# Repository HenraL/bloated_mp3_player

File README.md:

<!-- 
-- +==== BEGIN Bloated MP3 Player =================+
-- LOGO:
-- .......................
-- ...><>.............<><.
-- ..><>.><>.......<><.<><
-- .><>.<><.><>.<><.<><.<>
-- ..><>.><>.......<><.<><
-- ...><>.............<><.
-- .......................
-- /STOP
-- PROJECT: Bloated MP3 Player
-- FILE: README.md
-- CREATION DATE: 23-07-2026
-- LAST Modified: 14:19:29 01-09-2026
-- DESCRIPTION:
-- This is the code in charge of making the bloated player come to life.
-- /STOP
-- COPYRIGHT: (c) Henry Letellier
-- PURPOSE: This is the file that presents and explains the projects aim.
-- // AR
-- +==== END Bloated MP3 Player =================+
-->
# **DON'T PANIC**

## bloated_mp3_player

> **The answer is 42. The question, it turns out, is: "How many peripherals can you bolt onto an ESP32 before the scheduler files for divorce?"**

This is a multithreaded embedded project that started life as a humble MP3 player and, through a series of unfortunate events vaguely resembling a real-time systems course, accreted so many non-essential components that it now requires a concurrent scheduler just to keep them all arguing fairly for CPU time.

It runs on an ESP32-S3 (the electronic equivalent of an Infinite Improbability Drive, only slightly less likely to turn you into a potted plant or a philosophical whale), uses FreeRTOS under the hood (courtesy of the Arduino framework), and demonstrates that you can, in fact, teach concurrency by strapping seventeen unrelated sensors to a single I²C bus and hoping for the best.

## Contents

> *"Please read the signs before panic."*

- [About](#about) — why a Vogon would raise an eyebrow
- [Disclaimer](#disclaimer) — we tried to warn you
- [Dependencies](#dependencies) — the unhealthy soil it all grows in
- [Components Used](#components-used) — the BOM of doomed hardware
- [Divorce proceedings](#divorce-proceedings) — a strained peripheral marriage
- [How to Flash](#how-to-flash) — the very real thermonuclear toolchain
- [How to Use](#how-to-use) — but there is no off switch
- [Bonus Tools](#bonus-tools) — flamegraphs & baked fonts
- [License](#license) — so long, and thanks for all the fish

## About

> *"The ships hung in the sky in much the same way that bricks don't."*
> — Douglas Adams, *The Hitchhiker's Guide to the Galaxy*

This program is a multithreaded C++ monstrosity for the Real Time Embedded Systems course at **Unimore Enzo Ferrari AI and engineering department**. It was inspired by *The Hitchhiker's Guide to the Galaxy* not because it does anything particularly galactic, but because the sheer quantity of peripherals tacked onto it would make even a Vogon constructor fleet raise an eyebrow.

The core mission: play MP3s from a microSD card while simultaneously monitoring temperature, humidity, air pressure, rotation, acceleration, magnetic fields, and the existential dread of a WS2812B RGB matrix trying to decide what colour to be or where to put the bablefish.

Is it practical? No.
Does it demonstrate concurrency? Absolutely.
Would Zaphod Beeblebrox approve? Almost certainly, right before stealing it.

## Disclaimer

- This program is provided **as is**, without warranty of any kind — implied, express, or Vogon-constructed. If your ESP32 achieves sentience and demands a better quality MP3 files, that's your problem.
- This program was written with the assistance of AI. The AI is not responsible for any design decisions, but it did try to talk us out of the 16×16 RGB matrix. We didn't listen.
- Developed under **Ubuntu 24.04.4 LTS**, where ESP32s tend to materialise on `/dev/ttyACM0` (unless they're feeling contrary, in which case check `dmesg`).
- Targeted at the **ESP32-S3 WROOM FREENOVE** dev board. Flashed via the PlatformIO extension for VS Code (or however one normally communicates with small, irritable computers).
- The [KiCad schematic](./hardware/) is provided as a wiring reference. You could send it to a PCB manufacturer if you're feeling brave, but the author (and his AI accomplice) accept no responsibility for design issues, misplaced vias, or spontaneous combustion.
- Components are universally sourcable from websites such as Amazon, AliExpress, or (for the truly adventurous) by flagging down a passing Dentrassi supply ship.

## Dependencies

The software stack, from bottom to top:

| Layer | What it is | Why it's here |
| ------- | ----------- | --------------- |
| FreeRTOS | Real-time OS (via Arduino) | So 17 tasks can deadlock each other in style |
| Arduino ESP32 Core | HAL / framework | Because writing raw ESP-IDF is for people with more patience |
| [Adafruit NeoPixel](https://github.com/adafruit/Adafruit_NeoPixel) | RGB LED control | Makes the matrix glow reassuringly |
| [U8g2](https://github.com/olikraus/u8g2) | OLED/LCD monochrome graphics | Draws text and badly-scaled album art on the 128×64 LCD |
| [arduino-libhelix](https://github.com/pschatzmann/arduino-libhelix) | Fixed-point MP3 decoder | Helix-based MP3 decoding with PSRAM support; because software decoding without it is like a Vogon without a thesaurus |

Most library dependencies materialise automagically from the PlatformIO ether. The exception is the one that does the actual heavy lifting — see the submodule note below, and try not to think about what happens if you forget `--recursive`.

### Git Submodule: arduino-libhelix

> *"The major difference between a thing that might go wrong and a thing that cannot possibly go wrong is that when a thing that cannot possibly go wrong goes wrong, it usually turns out to be impossible to get at or repair."*
> — Douglas Adams, *Mostly Harmless*

This library lives at `platformio/bloated_mp3_player/lib/arduino-libhelix` and is not a PlatformIO registry package — it is, officially, A Thing That Cannot Possibly Go Wrong.

To initialise it (and thereby disprove the above quote):

```bash
git clone --recursive <repository-url>
```

If you cloned without `--recursive` (you magnificent fool):

```bash
git submodule update --init --recursive
```

PlatformIO scans `lib/` automatically, so the submodule compiles itself into the firmware with no further configuration. If this sounds too easy, re-read the quote at the top of this section.

## Components Used

> *"The Guide is definitive. Reality is frequently inaccurate."*
> — *The Hitchhiker's Guide to the Galaxy*

The following have been sacrificed on the altar of concurrency:

| Purpose | Name | Price (€) | Quantity | Link |
| --------- | ------ | ----------- | ---------- | ------ |
| :brain: The brains | Freenove ESP32-S3-WROOM CAM — Dual-core 32-bit 240 MHz | 20.19 | 1 | [AliExpress](https://aliexpress.com/item/1005004960637276.html) |
| :tv: Display | Lcd12864 12864-06D — COG dot matrix, SPI, with Chinese font | 6.19 | 1 | [AliExpress](https://aliexpress.com/item/1005009024477658.html) |
| :receipt: Cash-register display | TZT LCD2004+I2C — 2004A 20x4 HD44780 char LCD with I2C adapter soldered on the back | 4.85 | 1 | [AliExpress](https://aliexpress.com/item/1005004726086089.html) |
| :scroll: Vogon ticker | LCD1602+I2C Module — 16x2 HD44780 char LCD, PCF8574T IIC interface, 5 V (blue, I2C soldered on the back) | 2.63 | 1 | [AliExpress](https://aliexpress.com/item/1005006170395488.html) |
| :thermometer: Weather station | AHT20+BMP280 — Temperature, humidity & air pressure | 1.20 | 1 | [AliExpress](https://aliexpress.com/item/1005007702473893.html) |
| :triangular_ruler: Distance | HC-SR04 — Ultrasonic "how far is the wall" sensor | 1.41 | 1 | [AliExpress](https://aliexpress.com/item/1005007849944952.html) |
| :arrows_counterclockwise: User input | EC11 Rotary Encoder with switch — 20 positions, knob shaft | 3.49 | 1 | [AliExpress](https://aliexpress.com/item/1005004908084537.html) |
| :loud_sound: Crappy beeps | 4Ω 3W / 8Ω 2W cavity speaker — tiny, tinny, test-tones only | 1.38 | 2 | [AliExpress](https://aliexpress.com/item/1005008626624201.html) |
| :compass: Orientation | GY-9250 MPU-9250 — 9-axis gyro + accel + magnetometer | 3.09 | 1 | [AliExpress](https://aliexpress.com/item/1005007211455522.html) |
| :flashlight: Light show | WS2812B 16×16 RGB LED matrix — individually addressable chaos | 14.39 | 1 | [AliExpress](https://aliexpress.com/item/1005005394534715.html) |
| :floppy_disk: Storage | Micro SD Card Module — SPI level-shifted | 1.24 | 1 | [AliExpress](https://aliexpress.com/item/1005010653353565.html) |

**Total carnage:** ~€62.06 plus fuses, caps, and whatever else you inevitably forgot.

The two character displays (2004A + 1602A) arrive with their I2C adapter boards pre-soldered on the back, so no extra PCF8574 wiring is needed — just VCC/GND/SDA/SCL to the bus. Mind the addresses though: they ship defaulted to 0x27, so the second one needs the A0 pad bridged (0x26) to live on the same bus as the first.

For fuses, capacitors, resistors, and the 5 V → 3.3 V regulators, see the schematic. You probably have them in a drawer somewhere. The author assumes no responsibility for the state of that drawer.

### Divorce proceedings

> *"I am the President of the Galaxy. I'm not in the mood for a diplomatic relationship."*

Despite our best efforts, the development prototype has filed for divorce with two of its peripherals: the STN 128×64 LCD and the WS2812B matrix have gone silent (presumably due to wiring disagreements). The firmware driving both of them is still running, faithfully poking the pins every task tick — so if the wiring ever is reconciled, they may snap back to life like nothing happened. No firmware update required. Just cable therapy.

The I2C character displays, meanwhile, have fully reconciled: the 2004A info panel (folder browser, track names, volume, uptime) and the 1602A Vogon poetry panel (which also breathes IMU orientation readouts between stanzas) are both happily married to the bus. If the big LCD and matrix ever announce a reconciliation, this entry will be updated accordingly.

## How to Flash

> *"A towel is about the most massively useful thing an interstellar hitchhiker can have."*

1. Load some `.mp3` files onto a microSD card. 44.1 kHz, 16-bit stereo is the recommended flavour of the universe.
2. Insert the card into the ESP32's SD card reader (or the module you soldered on after muttering imprecations at the pinout).
3. Open the project in VS Code with the PlatformIO extension installed. If you don't have PlatformIO, you're about to have a Very Bad Time.
4. Connect your ESP32. There are usually two USB ports: one for UART (debug) and one for OTG (flash). **The OTG one is the one you want.** If you get it wrong, nothing explodes — you'll just get a timeout. This is fine.
5. Locate the **`→`** arrow at the bottom of the VS Code window. Click it. This compiles the firmware and, if the stars align, flashes it to the board.
6. If the flash fails: check the port, hold the BOOT button, and try again. Repeat until the universe stops playing tricks on you.

### Pre-flight flash erase

A PlatformIO extra script (`middleware/full_erase.py`) automatically erases the ESP32's flash before each upload. This ensures no stale data haunts your new firmware like the ghost of a Vogon poem.

It can also be run standalone:

```bash
python middleware/full_erase.py                          # auto-detect port
python middleware/full_erase.py --port /dev/ttyUSB0      # explicit port
```

It will find `esptool.py` in your PATH, or tell you to `pip install esptool` if you haven't.

## How to Use

> *"In the beginning, the universe was created. This has made a lot of people very angry and been widely regarded as a bad move."*

Turn the rotary encoder to navigate. Selection is two-stage: rotate to pick a
folder (album), press once to step inside and browse its tracks, rotate to the
track you want, press again to play it. Double- or triple-click the knob to skip
forward/back a track while playing (or to pop back to the album list while
browsing inside a folder). Wave a hand once past the ultrasonic sensor to pause,
and wave it twice quickly to abandon the current track and return to the menu.

The interface appears on the SPI LCD and the 2004A info panel, which shows the
current folder, track, volume and uptime (hh:mm:ss). The 1602A recites Vogon
poetry and periodically trades buffers with the IMU to show roll/pitch/yaw. The
RGB matrix will do something presumably artistic if its wiring ever gets talked
off the ledge. The ultrasonic sensor will judge your distance from the board.
The MPU-9250 will ponder its orientation in the cosmos. The temperature sensor
will inform you that it is, in fact, room temperature.

There is no off switch. You have been warned.

## Bonus Tools

### Flamegraph Profiling (bonus/extras/flamegraph.py)

The firmware includes a lightweight profiler that can dump task timing traces and CPU usage stats over the serial port. The `flamegraph.py` script converts that output into an interactive SVG flamegraph — a visual representation of where the CPU is spending its time (or, as the Guide would put it, "how the microprocessor is frittering away the microseconds").

**To capture profiling data:**

1. In the firmware, ensure `Profiling::dump_traces()` or `Profiling::dump_task_stats()` is called. The output appears on the serial console (typically 115200 baud) in sections bracketed by `=== PROFILING TRACES ===` / `=== END PROFILING TRACES ===`.
2. Save that serial output to a file:

   ```bash
   platformio device monitor --raw > serial_dump.txt
   ```

   Press the reset button to trigger the dump, then hit Ctrl+C to stop.
3. Generate the flamegraph:

   ```bash
   python bonus/extras/flamegraph.py serial_dump.txt
   ```

   This produces `flamegraph.svg` (or `flamegraph_traces.svg` / `flamegraph_task_stats.svg` if multiple sections are present).
4. Open the SVG in any browser. The wider a bar, the more time that function consumed. Hover for details.

**Usage summary:**

```bash
python bonus/extras/flamegraph.py < serial_dump.txt              # read from stdin
python bonus/extras/flamegraph.py serial_dump.txt                # read from file
python bonus/extras/flamegraph.py serial_dump.txt -o output.svg  # custom output
```

### Image & Font Conversion (bonus/ dir)

> *"The ships hung in the compiler's symbol table in much the same way that bricks don't."*
> — The Maker's Guide to the Codebase

Two Python converters that perform the digital equivalent of the Total Perspective Vortex:
they take your PNGs and TTF/OTF fonts, shrink them down to their essential C byte-array
essence, and embed them directly into the firmware. No filesystem reads. No SD card
dependency. Just pure, uncompromising, flash-resident data.

Use the provided shell scripts — they create their own virtual environment from
`requirements.txt`, install Pillow and fonttools, run the converter, then clean up
after themselves. Like a well-mannered Vogon butler.

| If you want to | Run this | It auto-creates venv from |
| --- | --- | --- |
| Bake fonts into C | `./bonus/font2c.sh` | `bonus/font2c/requirements.txt` |
| Bake images into C | `./bonus/img2c.sh` | `bonus/img2c/requirements.txt` |

---

#### Font → C (`bonus/font2c.sh` / `bonus/font2c/convert.py`)

Converts TTF/OTF fonts into a PlatformIO C library. Each glyph becomes a compact
bitmap; widths are proportional, the living is easy, and the flash usage is only
moderately horrifying.

**Quickest path to enlightenment:**

```bash
./bonus/font2c.sh
```

This processes every font in `bonus/fonts/` at point sizes 2 through 20 (step 2)
and deposits the resulting C library into `lib/fonts/`. The noise you hear is
Pillow rendering approximately 500 glyphs per size per font. Have a towel ready.

**Single font, specific size:**

```bash
./bonus/font2c.sh bonus/fonts/Tiny5/Tiny5-Regular.ttf lib/fonts/ --size 14
```

**What you can tweak:**

| Flag | Default | What it does (in plain Galactic) |
| ------ | --------- | ---------------------------------- |
| `--size SIZE` | — | Exactly one point size; ignores `--min`/`--max` |
| `--min MIN` | 8 | Smallest size to generate |
| `--max MAX` | 20 | Largest size to generate |
| `--step STEP` | 2 | Step between sizes (2 = 8, 10, 12, …) |
| `--first FIRST` | 32 (space) | First Unicode code point to include |
| `--last LAST` | 0x10FFFF | Last Unicode code point (yes, that's the whole of Unicode) |
| `--batch` | — | Recursively find all TTF/OTF in the input directory |
| `--no-extern` | — | Stuff everything into the headers (no separate .cpp) |
| `--no-progmem` | — | Omit PROGMEM (if you hate flash and love RAM) |

**What lands in `lib/fonts/`:**

```plaintext
lib/fonts/
├── include/
│   ├── fonts.hpp              — Master include (include this, get all)
│   ├── font_structs.hpp       — FontHandle, RenderedGlyph, and friends
│   ├── font_constants.hpp     — Size and style constants
│   ├── font_families.hpp      — Family cross-reference tables
│   ├── font_helpers.hpp       — find_font(), get_glyph() & co.
│   └── internal/<family>/
│       └── <family>_<size>pt.hpp  — Per-size declarations
├── src/
│   └── <family>_<size>pt.cpp  — Actual bit data + FontHandle
├── library.json
└── CMakeLists.txt
```

**Manual run (if you distrust shell scripts — and who can blame you?):**

```bash
python3 -m venv .venv
. .venv/bin/activate
pip install -r bonus/font2c/requirements.txt
python bonus/font2c/convert.py bonus/fonts/Tiny5/Tiny5-Regular.ttf lib/fonts/ --size 14
deactivate
```

---

#### Image → C (`bonus/img2c.sh` / `bonus/img2c/convert.py`)

Turns PNGs into C byte arrays. Each image gets two representations:

- **1-bit packed bitmap** — 8 pixels per byte, perfect for the 128×64 LCD
- **8-bit grayscale** — for when you eventually want to dither like a Vogon
  constructor fleet painting a bypass

**Quick start:**

```bash
./bonus/img2c.sh
```

Every PNG in `bonus/images/` gets converted and packed into `lib/images/` as a
PlatformIO library. If the images had towels, they'd be packed too.

**Single file:**

```bash
./bonus/img2c.sh bonus/images/baseline_menu_black_48dp.png --output lib/images/
```

**Available levers:**

| Flag | Default | Description |
| ------ | --------- | ------------- |
| `-o DIR`, `--output DIR` | — | Where to put the result |
| `--batch` | — | Process all PNGs in input directory |
| `--library` | — | Generate `include/` + `src/` PlatformIO structure |
| `--no-gray` | — | Skip the grayscale array |
| `--no-bits` | — | Skip the 1-bit packed array |
| `--gen-source FILE` | — | One `.cpp` to rule them all |
| `--no-extern` | — | Inline everything in headers |
| `--no-progmem` | — | No PROGMEM (RAM is a dish best served cold) |

**Output terrain:**

```plaintext
lib/images/
├── include/
│   ├── images.hpp                 — Aggregated master header
│   └── internal/
│       └── baseline_menu_black_48dp.hpp  — Per-image header
├── src/
│   └── images.cpp                 — Bit data definitions
├── library.json
└── CMakeLists.txt
```

**Manual run (for the autonomously inclined):**

```bash
python3 -m venv .venv
. .venv/bin/activate
pip install -r bonus/img2c/requirements.txt
python bonus/img2c/convert.py bonus/images/ lib/images/ --batch --library
deactivate
```

> **A note on virtual environments:**
> Your operating system's Python is a precious and temperamental ecosystem —
> rather like a Babel fish, but less useful at translating Vogon poetry.
> Do not install random packages into it. Use the shell scripts (they handle
> everything) or create a temporary venv manually. The universe will thank you.
> Probably.

## License

> *"So long, and thanks for all the fish."*

This project is licensed under the [MIT License](./LICENSE). Do what you like with it. If you build something cool, tell the dolphins.

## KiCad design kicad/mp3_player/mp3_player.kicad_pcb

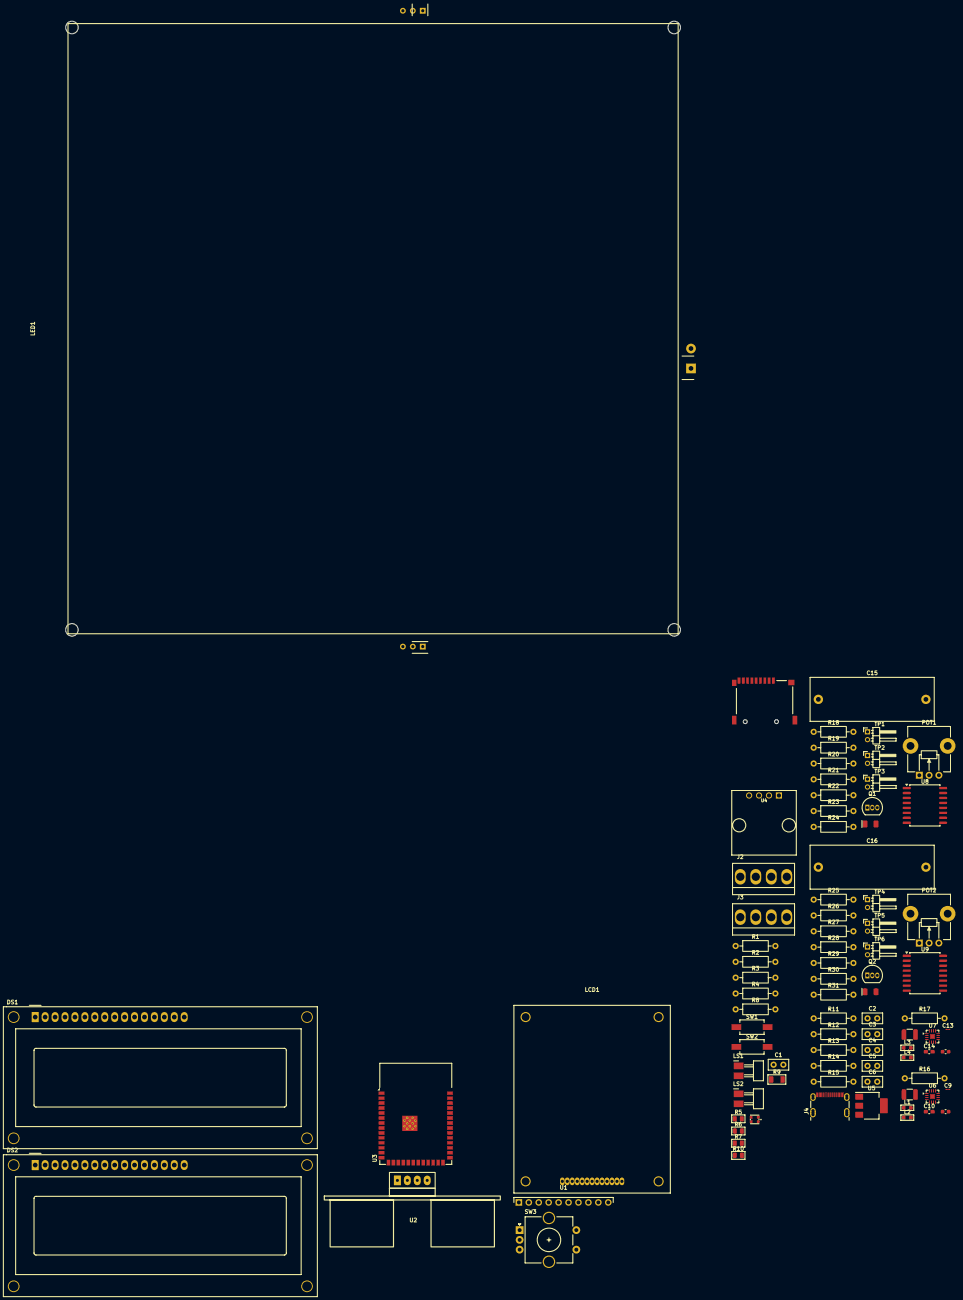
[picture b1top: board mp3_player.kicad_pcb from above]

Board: 2 copper layers, 86 parts (0 on the bottom side), 80 nets, no tracks yet.

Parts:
C1: 100nF_Ceramic; C_Disc_D5.0mm_W2.5mm_P2.50mm
C2: 1nF_Ceramic; C_Disc_D5.0mm_W2.5mm_P2.50mm
C3, C5: 10uF; C_Disc_D5.0mm_W2.5mm_P2.50mm
C4, C6: 100nF; C_Disc_D5.0mm_W2.5mm_P2.50mm
C7, C11: 10uF; C_1210_3225Metric
C8, C12: 0.1uF; C_0603_1608Metric
C9, C13: 220pF_0603_25V; C_01005_0402Metric_Pad0.57x0.30mm_HandSolder
C10, C14: 220pF_0603_25V; C_0603_1608Metric_Pad1.08x0.95mm_HandSolder
C15, C16: 0.1uF; C_Rect_L31.5mm_W11.0mm_P27.50mm_MKS4
D1: WS2812B; WS2812_2020
D2, D3: Blue; LED_1206_3216Metric_Blue
DS1: WC2004A; WC1602A
DS2: WC1602A
J1: microSD; microSD_External_Pin
J2, J3: Conn_01x04; Pins_1x04_3.96mm_TH_MTA156
J4: Conn_USB_C_Socket; Conn_USB_C_Socket_Molex_2171790001
L1, L2, L3, L4: 33nH; R_0603_1608Metric_Pad0.98x0.95mm_HandSolder
LCD1: LCD-13pin; LCD_1x13_P1.27mm_Vertical
LED1: LED_Matrix_16x16_WS2812B
LS1, LS2: Speaker; PinHeader_01x02_P2.54mm_Horizontal_SMD
POT1, POT2: 16mm_CtrDet_10k; Potentiometer_TT_P0915N
Q1, Q2: S8050; TO-92_Inline
R1: 2.2k; R_Axial_DIN0207_L6.3mm_D2.5mm_P10.16mm_Horizontal
R2, R18, R19, R20, R22, R25, R26, R27, R29: 1k; R_Axial_DIN0207_L6.3mm_D2.5mm_P10.16mm_Horizontal
R3, R4: 4.7k; R_Axial_DIN0207_L6.3mm_D2.5mm_P10.16mm_Horizontal
R5, R6, R7, R10: R_0805; R_0805_2012Metric
R8: 220ohm; R_Axial_DIN0207_L6.3mm_D2.5mm_P10.16mm_Horizontal
R9: R_1206; R_1206_3216Metric
R11, R16, R17: 1M; R_Axial_DIN0207_L6.3mm_D2.5mm_P10.16mm_Horizontal
R12, R13: 5.1k; R_Axial_DIN0207_L6.3mm_D2.5mm_P10.16mm_Horizontal
R14, R15: 10k; R_Axial_DIN0207_L6.3mm_D2.5mm_P10.16mm_Horizontal
R21, R23, R24, R28, R30, R31: 47k; R_Axial_DIN0207_L6.3mm_D2.5mm_P10.16mm_Horizontal
SW1: Boot; Button_CnK_PTS636.0_6x3.5mm
SW2: Reset; Button_CnK_PTS636.0_6x3.5mm
SW3: RotaryEncoder_Switch; RotaryEncoder_Alps_EC11E-Switch_Vertical_H20mm_CircularMoun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
TP1, TP2, TP3, TP4, TP5, TP6: TestPoint_2Pole; PinHeader_1x02_P2.00mm_Horizontal
U1: MPU6500-breakout; GY-6500_1x10_P2.54mm_Vertical
U2: HC-SR04_Ultrasonic_Sensor
U3: ESP32-S3-WROOM-1
U4: AHT20_BMP280
U5: AMS1117-3.3; SOT-223-3_TabPin2
U6, U7: MAX98357A; TQFN-16-1EP_3x3mm_P0.5mm_EP1.23x1.23mm
U8, U9: PCF8574T; SOIC-16W_7.5x10.3mm_P1.27mm

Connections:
5V: C3.1, C7.2, C8.2, C11.2, C12.2, C15.1, C16.1, D2.2 (A), D3.2 (A), DS1.2 (VDD), DS1.15 (LED(+)), DS2.2 (VDD), J2.2, J3.2, J4.A4 (VBUS), J4.A9 (VBUS), J4.B4 (VBUS), J4.B9 (VBUS), LED1.1 (5V_IN), POT1.1 (Left), POT2.1 (Left), R16.1, R16.2, R17.1, R17.2, R19.1, R20.1, R21.2, R22.1, R23.2, R24.1, R26.1, R27.1, R28.2, R29.1, R30.2, R31.1, U2.1 (VCC), U6.4 (~SD_MODE), U6.7 (VDD), U6.8 (VDD), U7.4 (~SD_MODE), U7.7 (VDD), U7.8 (VDD), U8.16 (VDD), U9.16 (VDD)
/ESP power/EN: R14.2, SW2.2
/ESP power/ESP32_USB_D+: J4.A6 (Dp1), J4.B7 (Dn2), U3.14 (USB_D+)
/ESP power/ESP32_USB_D-: J4.A7 (Dn1), J4.B6 (Dp2), U3.13 (USB_D-)
/ESP power/IO0: R15.2, SW1.2
/I2C1/(K) BL-: DS1.16 (LED(-)), Q2.3 (C)
/I2C1/A0: R26.2, TP4.1, U9.1 (A0)
/I2C1/A1: R27.2, TP5.1, U9.2 (A1)
/I2C1/A2: R29.2, TP6.1, U9.3 (A2)
/I2C1/DB4: DS1.11 (D4), U9.9 (P4)
/I2C1/DB5: DS1.12 (D5), U9.10 (P5)
/I2C1/DB6: DS1.13 (D6), U9.11 (P6)
/I2C1/DB7: DS1.14 (D7), U9.12 (P7)
/I2C1/E: DS1.6 (E), U9.6 (P2)
/I2C1/RS: DS1.4 (RS), U9.4 (P0)
/I2C1/R/W: DS1.5 (R/W), U9.5 (P1)
/I2C1/V0: DS1.3 (VO), POT2.2 (Center)
/I2C/(K) BL-: DS2.16 (LED(-)), Q1.3 (C)
/I2C/A0: R19.2, TP1.1, U8.1 (A0)
/I2C/A1: R20.2, TP2.1, U8.2 (A1)
/I2C/A2: R22.2, TP3.1, U8.3 (A2)
/I2C/DB4: DS2.11 (D4), U8.9 (P4)
/I2C/DB5: DS2.12 (D5), U8.10 (P5)
/I2C/DB6: DS2.13 (D6), U8.11 (P6)
/I2C/DB7: DS2.14 (D7), U8.12 (P7)
/I2C/E: DS2.6 (E), U8.6 (P2)
/I2C/RS: DS2.4 (RS), U8.4 (P0)
/I2C/R/W: DS2.5 (R/W), U8.5 (P1)
/I2C/SCL: J2.4, J3.4, R3.1, R23.1, R30.1, U1.3 (SCL), U1.6 (ECL), U3.39 (IO1), U4.SCL, U8.14 (SCL), U9.14 (SCL)
/I2C/SDA: J2.3, J3.3, R4.1, R21.1, R28.1, U1.4 (SDA), U1.5 (EDA), U3.38 (IO2), U4.SDA, U8.15 (SDA), U9.15 (SDA)
/I2C/V0: DS2.3 (VO), POT1.2 (Center)
/MAX98357/BCLK: U3.9 (IO16), U6.16 (BCLK), U7.16 (BCLK)
/MAX98357/DIN: U3.11 (IO18), U7.1 (DIN)
/MAX98357/LRCLK: U3.24 (IO47), U6.14 (LRCLK), U7.14 (LRCLK)
/MAX98357/VD+: C13.1, L3.2, LS2.1
/MAX98357/VD-: C14.1, L4.2, LS2.2
/MAX98358/DIN: U3.10 (IO17), U6.1 (DIN)
/MAX98358/VD+: C9.1, L1.2, LS1.1
/MAX98358/VD-: C10.1, L2.2, LS1.2
GND: C2.1, C4.1, C7.1, C8.1, C9.2, C10.2, C11.1, C12.1, C13.2, C14.2, C15.2, C16.2, D1.2 (VSS), DS1.1 (VSS), DS2.1 (VSS), J1.6 (VSS), J1.10 (SHIELD), J2.1, J3.1, J4.A1 (GND), J4.A12 (GND), J4.B1 (GND), J4.B12 (GND), LCD1.7 (VSS), LCD1.9 (K), LED1.3 (GND_IN), LED1.6 (GND_OUT), LED1.8 (GND), POT1.3 (Right), POT2.3 (Right), Q1.1 (E), Q2.1 (E), R1.1, R11.1, R12.2, R13.2, R18.1, R25.1, SW3.C, SW3.S1, TP1.2, TP2.2, TP3.2, TP4.2, TP5.2, TP6.2, U1.2 (GND), U1.7 (AD0), U1.10 (FSYNC), U2.4 (GND), U3.1 (GND), U3.40 (GND), U3.41 (GND), U4.GND, U5.2 (GND), U6.3 (GND), U6.11 (GND), U6.15 (GND), U6.17 (PAD), U7.3 (GND), U7.11 (GND), U7.15 (GND), U7.17 (PAD), U8.8 (GND), U9.8 (GND)
unnamed: C4.2, C5.1
unnamed: D1.3 (DIN), U3.25 (IO48)
unnamed: D2.1 (K), R18.2
unnamed: D3.1 (K), R25.2
unnamed: J1.5 (CLK/SCK), R6.2
unnamed: C1.1, J1.3 (CMD/SDI), R7.2, R9.2
unnamed: J1.7 (DAT0/SDO), R5.2, R10.2
unnamed: J4.A5 (CC1), R12.1
unnamed: J4.B5 (CC2), R13.1
unnamed: C2.2, J4.S1 (SHIELD), R11.2
unnamed: LCD1.8 (A), R8.2
unnamed: LCD1.1 (CS), U3.18 (IO10)
unnamed: LCD1.11 (IC_CS), U3.5 (IO5)
unnamed: LCD1.12 (IC_S0), U3.4 (IO4)
unnamed: LCD1.5 (SI), LCD1.13 (IC_S1), U3.6 (IO6)
unnamed: LCD1.4 (SCL), LCD1.10 (IC_SCL), U3.7 (IO7)
unnamed: LCD1.3 (RS), U3.12 (IO8)
unnamed: LCD1.2 (RSE), U3.17 (IO9)
unnamed: LED1.2 (DIN), U3.34 (IO41)
unnamed: Q1.2 (B), R24.2, U8.7 (P3)
unnamed: Q2.2 (B), R31.2, U9.7 (P3)
unnamed: U1.8 (INT), U3.19 (IO11)
unnamed: R2.1, U2.3 (ECHO)
unnamed: U2.2 (TRIG), U3.22 (IO14)
unnamed: SW2.1, U3.3 (EN)
unnamed: SW1.1, U3.27 (IO0)
unnamed: SW3.S2, U3.20 (IO12)
unnamed: R1.2, R2.2, U3.21 (IO13)
unnamed: SW3.B, U3.8 (IO15)
unnamed: R7.1, U3.31 (IO38)
unnamed: R6.1, U3.32 (IO39)
unnamed: R5.1, U3.33 (IO40)
unnamed: SW3.A, U3.35 (IO42)
unnamed: C3.2, U5.1 (IN)
unnamed: C6.1, U5.3 (OUT)
unnamed: L2.1, U6.10 (OUTN)
unnamed: L1.1, U6.9 (OUTP)
unnamed: L4.1, U7.10 (OUTN)
unnamed: L3.1, U7.9 (OUTP)
PWR_3V3: C1.2, C5.2, C6.2, D1.4 (VDD), J1.4 (VDD), LCD1.6 (VDD), R3.2, R4.2, R8.1, R9.1, R10.1, R14.1, R15.1, U1.1 (VCC), U1.9 (NCS), U3.2 (3V3), U4.VDD
